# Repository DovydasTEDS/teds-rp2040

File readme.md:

# TEDS RP2040

an rp2040 devboard. GPIO pinouts should be the same as / similar to the pi pico, with a few extra pins  
there is also an LED which could be used as a status indicator  

routing the PCB was a pain... especially since the footprint for the flash was bigger than the easy EasyRP2040 guide  
both usb routes are the same distance like required  

Schematic            |  PCB         |   PCB (3d)
:-------------------------:|:-------------------------:|:-------------------------:|
    |    |

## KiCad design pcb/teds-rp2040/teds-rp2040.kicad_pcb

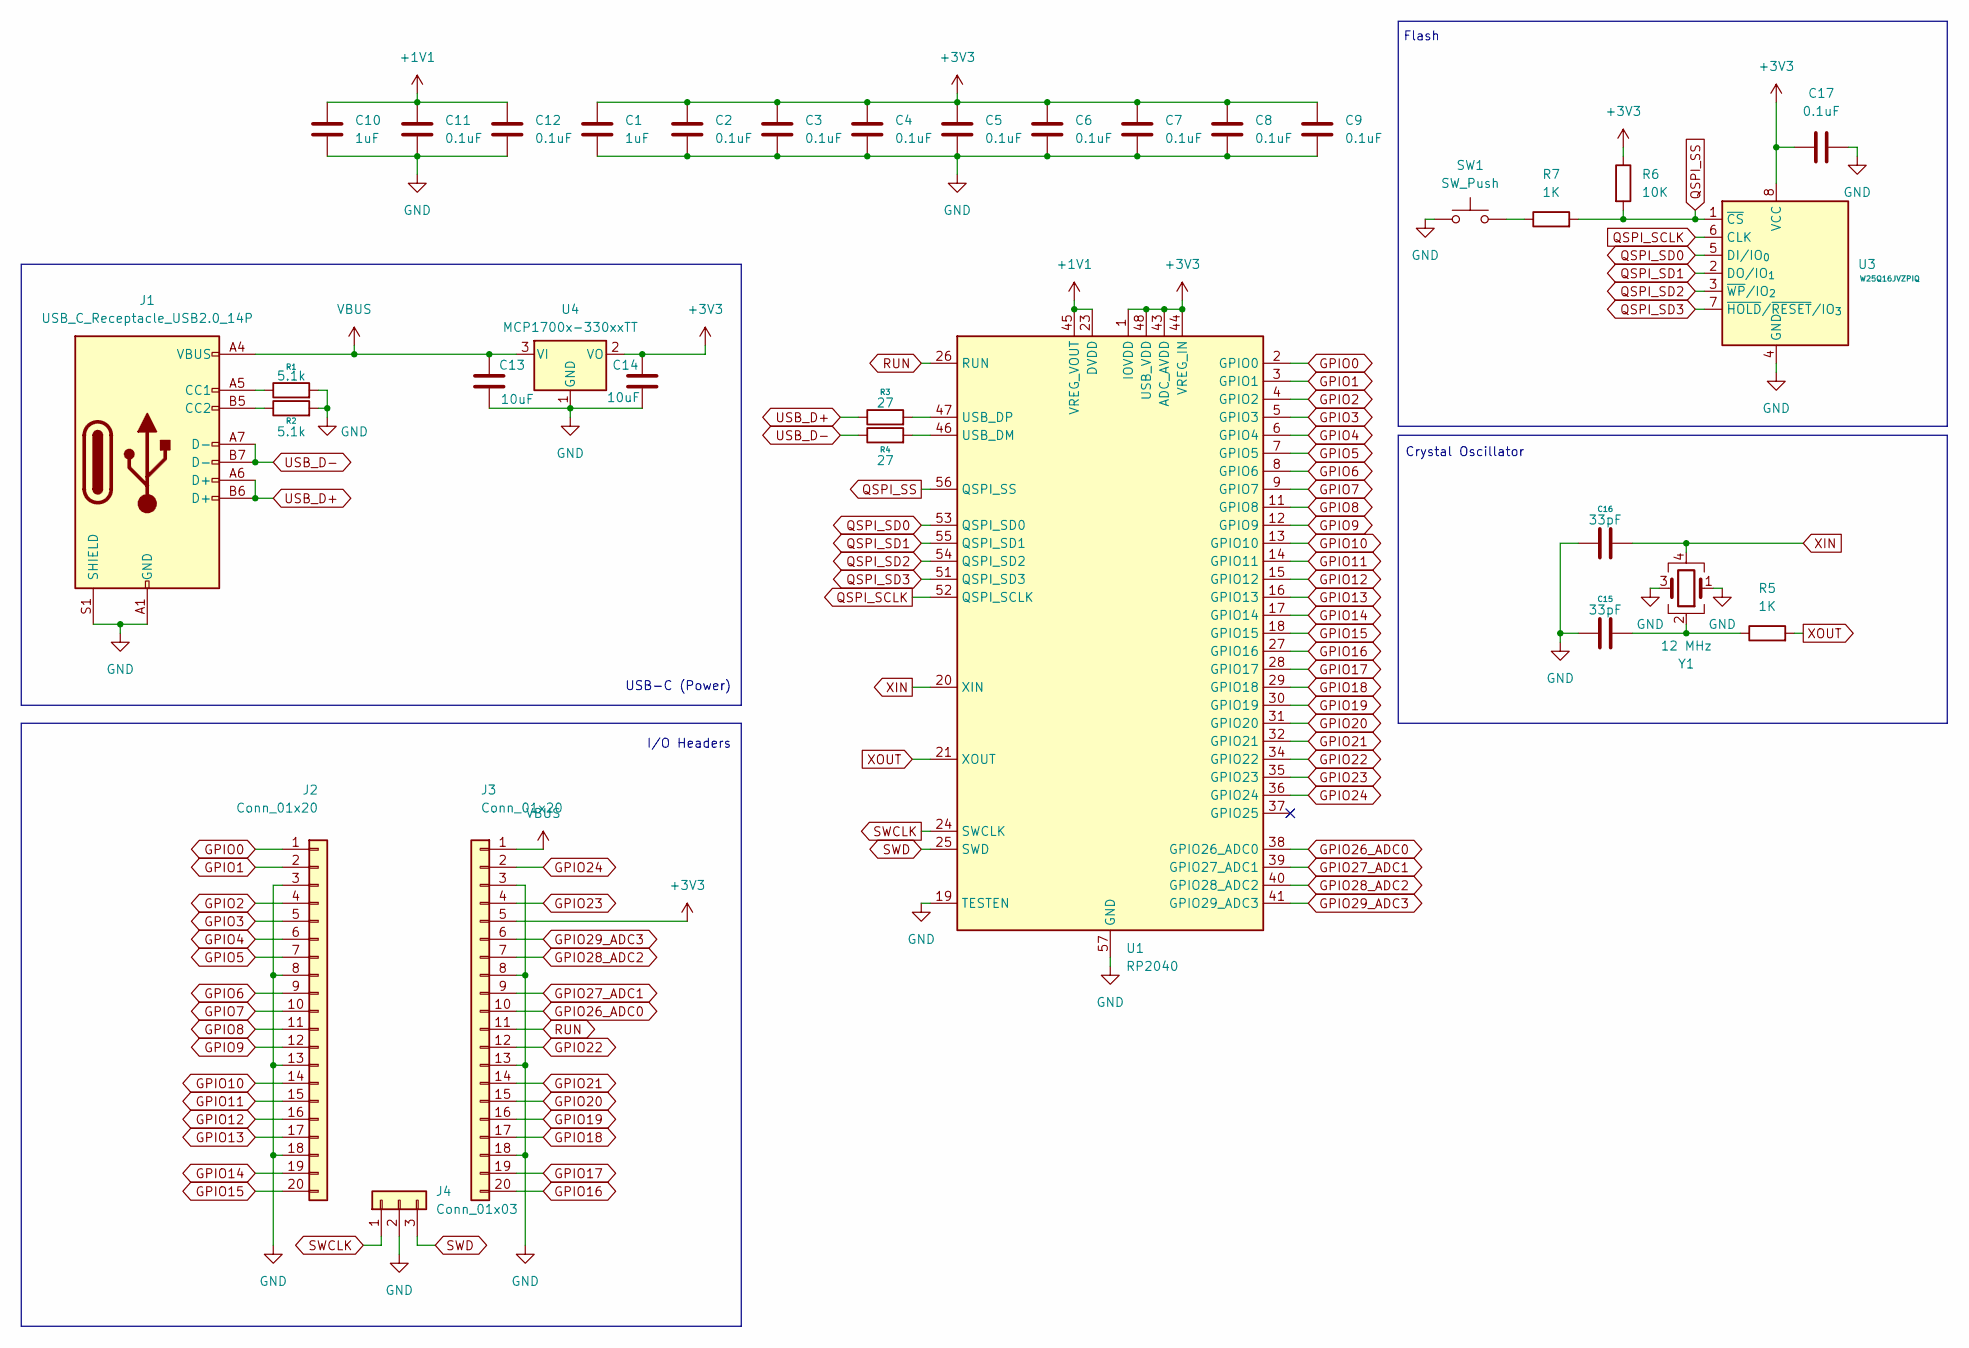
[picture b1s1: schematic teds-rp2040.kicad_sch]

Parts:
C1, C10: 1uF; C_0402_1005Metric
C2, C3, C4, C5, C6, C7, C8, C9, C11, C12, C17: 0.1uF; C_0402_1005Metric
C13, C14: 10uF; C_0603_1608Metric
C15, C16: 33pF; C_0402_1005Metric
J1: USB_C_Receptacle_USB2.0_14P; USB_C_Receptacle_HRO_TYPE-C-31-M-12
J2, J3: Conn_01x20; PinHeader_1x20_P2.54mm_Vertical
J4: Conn_01x03; PinHeader_1x03_P2.54mm_Vertical
R1, R2: 5.1k; R_0402_1005Metric
R3, R4: 27; R_0402_1005Metric
R5, R7: 1K; R_0402_1005Metric
R6: 10K; R_0402_1005Metric
SW1: SW_Push; SW_Push_SPST_NO_Alps_SKRK
U1: RP2040; QFN-56-1EP_7x7mm_P0.4mm_EP3.2x3.2mm
U3: W25Q16JVZPIQ; SON127P500X600X80-9N
U4: MCP1700x-330xxTT; SOT-23
Y1: 12 MHz; Crystal_SMD_3225-4Pin_3.2x2.5mm

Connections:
+1V1: C10.1, C11.1, C12.1, U1.23 (DVDD), U1.45 (VREG_VOUT), U1.50 (DVDD)
+3V3: C1.1, C2.1, C3.1, C4.1, C5.1, C6.1, C7.1, C8.1, C9.1, C14.1, C17.1, J3.5, R6.1, U1.1 (IOVDD), U1.10 (IOVDD), U1.22 (IOVDD), U1.33 (IOVDD), U1.42 (IOVDD), U1.43 (ADC_AVDD), U1.44 (VREG_IN), U1.48 (USB_VDD), U1.49 (IOVDD), U3.8 (VCC), U4.2 (VO)
GND: C1.2, C2.2, C3.2, C4.2, C5.2, C6.2, C7.2, C8.2, C9.2, C10.2, C11.2, C12.2, C13.2, C14.2, C15.1, C16.1, C17.2, J1.A1 (GND), J1.A12 (GND), J1.B1 (GND), J1.B12 (GND), J1.S1 (SHIELD), J2.3, J2.8, J2.13, J2.18, J3.3, J3.8, J3.13, J3.18, J4.2, R1.2, R2.2, SW1.1, U1.19 (TESTEN), U1.57 (GND), U3.4 (GND), U4.1 (GND), Y1.1, Y1.3
GPIO0: J2.1, U1.2 (GPIO0)
GPIO1: J2.2, U1.3 (GPIO1)
GPIO2: J2.4, U1.4 (GPIO2)
GPIO3: J2.5, U1.5 (GPIO3)
GPIO4: J2.6, U1.6 (GPIO4)
GPIO5: J2.7, U1.7 (GPIO5)
GPIO6: J2.9, U1.8 (GPIO6)
GPIO7: J2.10, U1.9 (GPIO7)
GPIO8: J2.11, U1.11 (GPIO8)
GPIO9: J2.12, U1.12 (GPIO9)
GPIO10: J2.14, U1.13 (GPIO10)
GPIO11: J2.15, U1.14 (GPIO11)
GPIO12: J2.16, U1.15 (GPIO12)
GPIO13: J2.17, U1.16 (GPIO13)
GPIO14: J2.19, U1.17 (GPIO14)
GPIO15: J2.20, U1.18 (GPIO15)
GPIO16: J3.20, U1.27 (GPIO16)
GPIO17: J3.19, U1.28 (GPIO17)
GPIO18: J3.17, U1.29 (GPIO18)
GPIO19: J3.16, U1.30 (GPIO19)
GPIO20: J3.15, U1.31 (GPIO20)
GPIO21: J3.14, U1.32 (GPIO21)
GPIO22: J3.12, U1.34 (GPIO22)
GPIO23: J3.4, U1.35 (GPIO23)
GPIO24: J3.2, U1.36 (GPIO24)
GPIO26_ADC0: J3.10, U1.38 (GPIO26_ADC0)
GPIO27_ADC1: J3.9, U1.39 (GPIO27_ADC1)
GPIO28_ADC2: J3.7, U1.40 (GPIO28_ADC2)
GPIO29_ADC3: J3.6, U1.41 (GPIO29_ADC3)
unnamed: C15.2, R5.1, Y1.2
unnamed: J1.A5 (CC1), R1.1
unnamed: J1.B5 (CC2), R2.1
unnamed: R7.1, SW1.2
unnamed: R4.2, U1.46 (USB_DM)
unnamed: R3.2, U1.47 (USB_DP)
QSPI_SCLK: U1.52 (QSPI_SCLK), U3.6 (CLK)
QSPI_SD0: U1.53 (QSPI_SD0), U3.5 (DI/IO_{0})
QSPI_SD1: U1.55 (QSPI_SD1), U3.2 (DO/IO_{1})
QSPI_SD2: U1.54 (QSPI_SD2), U3.3 (~WP/IO_{2})
QSPI_SD3: U1.51 (QSPI_SD3), U3.7 (~HOLD/~RESET/IO_{3})
QSPI_SS: R6.2, R7.2, U1.56 (QSPI_SS), U3.1 (~CS)
RUN: J3.11, U1.26 (RUN)
SWCLK: J4.1, U1.24 (SWCLK)
SWD: J4.3, U1.25 (SWD)
USB_D+: J1.A6 (D+), J1.B6 (D+), R3.1
USB_D-: J1.A7 (D-), J1.B7 (D-), R4.1
VBUS: C13.1, J1.A4 (VBUS), J1.A9 (VBUS), J1.B4 (VBUS), J1.B9 (VBUS), J3.1, U4.3 (VI)
XIN: C16.2, U1.20 (XIN), Y1.4
XOUT: R5.2, U1.21 (XOUT)

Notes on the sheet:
Crystal Oscillator
I/O Headers
USB-C (Power)
Flash

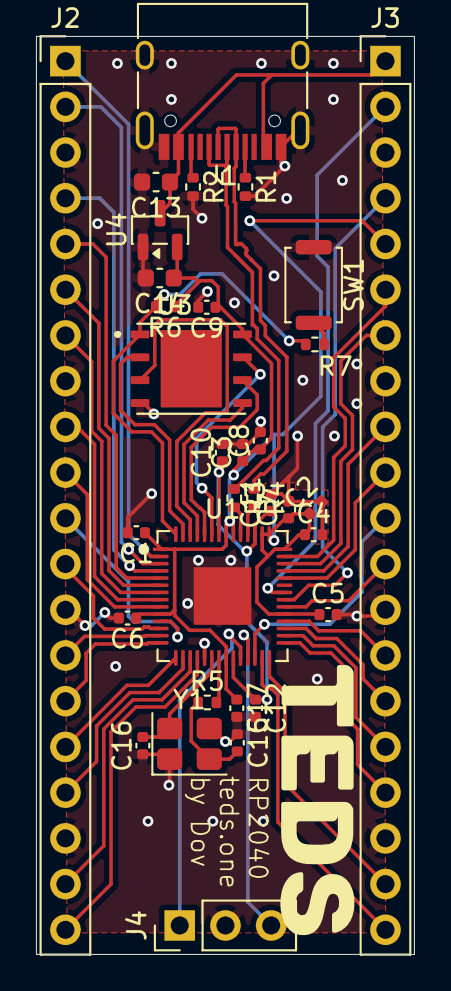
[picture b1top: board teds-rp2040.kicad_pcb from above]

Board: 2 copper layers, 21.0 x 51.0 mm, 33 parts (0 on the bottom side), 52 nets.

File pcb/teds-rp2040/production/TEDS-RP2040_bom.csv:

Designator,Footprint,Quantity,Value,LCSC Part #
"C1, C10",0402,2,1uF,
"C11, C12, C17, C2, C3, C4, C5, C6, C7, C8, C9",0402,11,0.1uF,
"C13, C14",0603,2,10uF,
"C15, C16",0402,2,33pF,
J1,USB_C_Receptacle_HRO_TYPE-C-31-M-12,1,USB_C_Receptacle_USB2.0_14P,
"J2, J3",PinHeader_1x20_P2.54mm_Vertical,2,Conn_01x20,
J4,PinHeader_1x03_P2.54mm_Vertical,1,Conn_01x03,
"R1, R2",0402,2,5.1k,
"R3, R4",0402,2,27,
"R5, R7",0402,2,1K,
R6,0402,1,10K,
SW1,SW_Push_SPST_NO_Alps_SKRK,1,SW_Push,
U1,QFN-56-1EP_7x7mm_P0.4mm_EP3.2x3.2mm,1,RP2040,
U3,SON127P500X600X80-9N,1,W25Q16JVZPIQ,
U4,SOT-23,1,MCP1700x-330xxTT,
Y1,Crystal_SMD_3225-4Pin_3.2x2.5mm,1,12 MHz,

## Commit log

2025-12-30 create
2026-01-03 Make it work
2026-01-03 add BOM from jlcpcb
2026-01-03 add production folder in project root
2026-01-07 add led
